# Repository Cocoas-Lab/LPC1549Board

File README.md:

# LPC1549 Develpment Board  

小型で安価なLPCボードの開発を目指しています  

## 機能
* USBからのバスパワー給電に対応
* 保護ICによるUSB短絡保護
* COMPortを介した書き込みに対応し, 別途書き込み機が不要 
* 5[V], 3.3[V]の2レベル電源出力 
* 22本の独立したGPIO
* 3個のオンチップLED
* 1個のユーザーボタン
* AD変換用に2.5[V]リファレンスを搭載

## イメージ
  
上から見た画像  

下から見た画像

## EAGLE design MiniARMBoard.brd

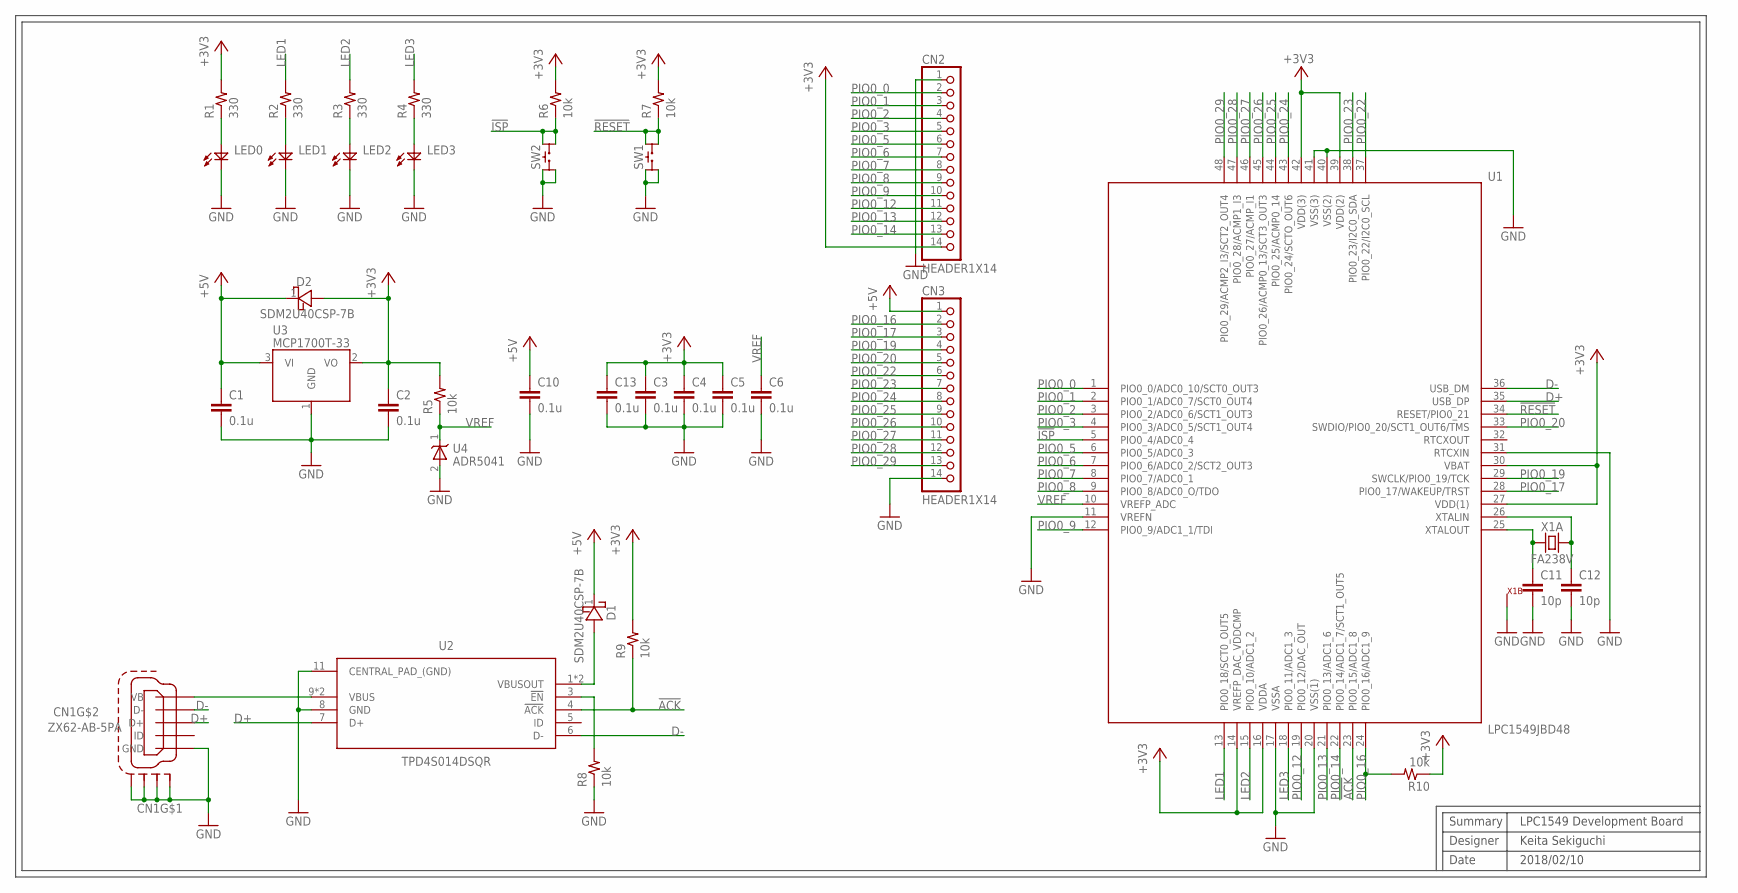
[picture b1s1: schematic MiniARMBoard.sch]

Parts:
C1, C2, C3, C4, C5, C6, C10, C13: 0.1u; C1005
C11, C12: 10p; C1005
CN1: ZX62-AB-5PA; J_USB_MICROAB_HIROSE_ZX62-AB-5PA
CN2, CN3: HEADER1X14; 1X14_ROUND
D1, D2: SDM2U40CSP-7B; X3-WLB1608-2
LED0, LED1, LED2, LED3: LED1608
R1, R2, R3, R4: 330; R1005
R5, R6, R7, R8, R9, R10: 10k; R1005
SW1, SW2: SKRP
U1: LPC1549JBD48; QFP48
U2: TPD4S014DSQR; SON40P200X200X80-11N
U3: MCP1700T-33; SOT23-3
U4: ADR5041; SC70-3
X1: FA238V; EPSON_FA238V

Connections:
!ACK: R9.1, U1.23 (PIO0_15/ADC1_8), U2.4 (!ACK)
!ISP: R6.1, SW2.B1, SW2.B2, U1.5 (PIO0_4/ADC0_4)
!RESET: R7.1, SW1.B1, SW1.B2, U1.34 (RESET/PIO0_21)
+3V3: C2.1, C3.1, C4.1, C5.1, C13.1, CN2.14, D2.2 (A), R1.2, R5.2, R6.2, R7.2, R9.2, R10.1, U1.14 (VREFP_DAC_VDDCMP), U1.16 (VDDA), U1.27 (VDD(1)), U1.30 (VBAT), U1.39 (VDD(2)), U1.42 (VDD(3)), U3.2 (VO)
+5V: C1.1, C10.1, CN3.1, D1.1 (K), D2.1 (K), U3.3 (VI)
D+: CN1.P$3 (D+), U1.35 (USB_DP), U2.7 (D+)
D-: CN1.P$2 (D-), U1.36 (USB_DM), U2.6 (D-)
GND: C1.2, C2.2, C3.2, C4.2, C5.2, C6.2, C10.2, C11.2, C12.2, C13.2, CN1.P$5 (GND), CN1.SHIELD1 (S1), CN1.SHIELD2 (S2), CN1.SHIELD3 (S3), CN1.SHIELD4 (S4), CN2.1, CN3.14, LED0.K, LED1.K, LED2.K, LED3.K, R8.1, SW1.A1, SW1.A2, SW2.A1, SW2.A2, U1.11 (VREFN), U1.17 (VSSA), U1.20 (VSS(1)), U1.31 (RTCXIN), U1.40 (VSS(2)), U1.41 (VSS(3)), U2.8 (GND), U2.11 (CENTRAL_PAD_(GND)), U3.1 (GND), U4.2 (A), X1.2 (1), X1.4 (1)
LED1: R2.2, U1.13 (PIO0_18/SCT0_OUT5)
LED2: R3.2, U1.15 (PIO0_10/ADC1_2)
LED3: R4.2, U1.18 (PIO0_11/ADC1_3)
unnamed: C11.1, U1.25 (XTALOUT), X1.1
unnamed: C12.1, U1.26 (XTALIN), X1.3
unnamed: D1.2 (A), U2.1 (VBUSOUT), U2.2 (VBUSOUT)
unnamed: R8.2, U2.3 (!EN)
unnamed: LED0.A, R1.1
unnamed: LED2.A, R3.1
unnamed: LED3.A, R4.1
unnamed: LED1.A, R2.1
unnamed: CN1.P$1 (VB), U2.9 (VBUS), U2.10 (VBUS)
PIO0_0: CN2.2, U1.1 (PIO0_0/ADC0_10/SCT0_OUT3)
PIO0_1: CN2.3, U1.2 (PIO0_1/ADC0_7/SCT0_OUT4)
PIO0_2: CN2.4, U1.3 (PIO0_2/ADC0_6/SCT1_OUT3)
PIO0_3: CN2.5, U1.4 (PIO0_3/ADC0_5/SCT1_OUT4)
PIO0_5: CN2.6, U1.6 (PIO0_5/ADC0_3)
PIO0_6: CN2.7, U1.7 (PIO0_6/ADC0_2/SCT2_OUT3)
PIO0_7: CN2.8, U1.8 (PIO0_7/ADC0_1)
PIO0_8: CN2.9, U1.9 (PIO0_8/ADC0_O/TDO)
PIO0_9: CN2.10, U1.12 (PIO0_9/ADC1_1/TDI)
PIO0_12: CN2.11, U1.19 (PIO0_12/DAC_OUT)
PIO0_13: CN2.12, U1.21 (PIO0_13/ADC1_6)
PIO0_14: CN2.13, U1.22 (PIO0_14/ADC1_7/SCT1_OUT5)
PIO0_16: CN3.2, R10.2, U1.24 (PIO0_16/ADC1_9)
PIO0_17: CN3.3, U1.28 (PIO0_17/WAKEUP/TRST)
PIO0_19: CN3.4, U1.29 (SWCLK/PIO0_19/TCK)
PIO0_20: CN3.5, U1.33 (SWDIO/PIO0_20/SCT1_OUT6/TMS)
PIO0_22: CN3.6, U1.37 (PIO0_22/I2C0_SCL)
PIO0_23: CN3.7, U1.38 (PIO0_23/I2C0_SDA)
PIO0_24: CN3.8, U1.43 (PIO0_24/SCTO_OUT6)
PIO0_25: CN3.9, U1.44 (PIO0_25/ACMP0_14)
PIO0_26: CN3.10, U1.45 (PIO0_26/ACMP0_13/SCT3_OUT3)
PIO0_27: CN3.11, U1.46 (PIO0_27/ACMP_I1)
PIO0_28: CN3.12, U1.47 (PIO0_28/ACMP1_I3)
PIO0_29: CN3.13, U1.48 (PIO0_29/ACMP2_I3/SCT2_OUT4)
VREF: C6.1, R5.1, U1.10 (VREFP_ADC), U4.1 (K)

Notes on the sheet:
Keita Sekiguchi
Summary
LPC1549 Development Board
Designer
Date
2018/02/10

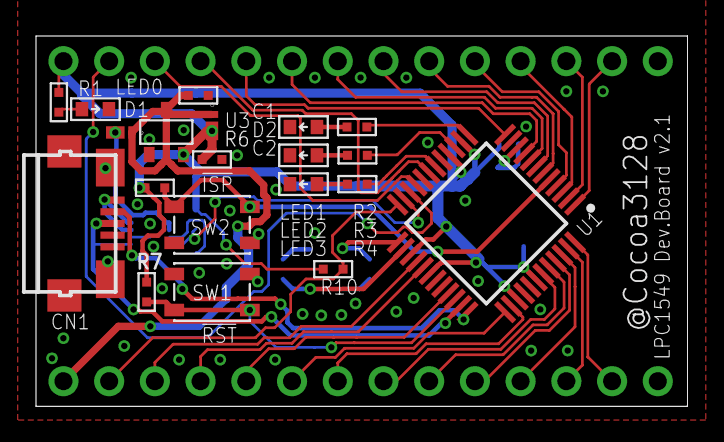
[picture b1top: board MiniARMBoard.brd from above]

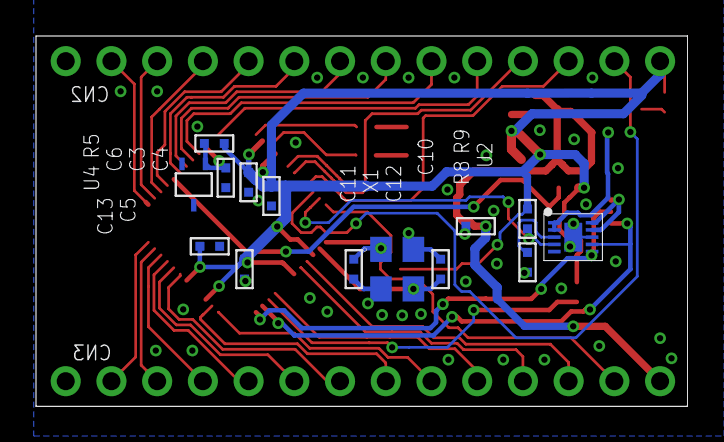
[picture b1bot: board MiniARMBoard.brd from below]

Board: 2 copper layers, 36.2 x 20.6 mm, 36 parts (14 on the bottom side), 45 nets.

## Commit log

2017-12-23 LPCボードの第一回発注
2017-12-27 elecrowの指示による訂正
2018-01-07 gitignoreの更新
2018-01-07 パーツ変更
    USBの保護をRFからICに
    シリアル変換ICをFT234XDに
2018-01-23 集積化を進めた
2018-02-10 シルクの調整を行なった
2018-02-10 ICの名前を'IC*'から'U*'に変更
2018-02-10 FusionSincで変更されたやつ
2018-02-10 発注時のgerver
2018-02-18 部品表の更新
2018-02-18 readme.mdを追加
2018-02-18 キャプションの改行
2018-03-07 回路図の見た目を整えてみた
2018-04-03 [fix]usb-dfu仕様に変更
2018-04-03 [fix]未保存分
